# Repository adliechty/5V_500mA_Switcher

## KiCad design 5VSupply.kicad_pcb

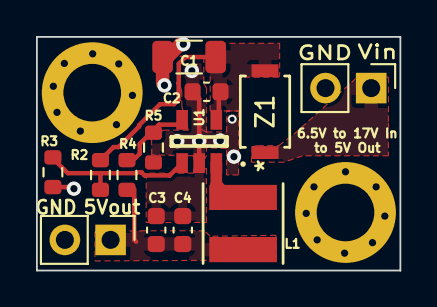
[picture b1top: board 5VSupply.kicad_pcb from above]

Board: 2 copper layers, 20.2 x 13.0 mm, 15 parts (0 on the bottom side), 7 nets.

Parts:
C1: 22uF; C_1206_3216Metric
C2: 0.1uF; C_0603_1608Metric
C3, C4: 10uF; C_0603_1608Metric
H1, H2: DNP; MountingHole_3.2mm_M3_DIN965_Pad
J1, J2: Conn_01x02; PinHeader_1x02_P2.54mm_Vertical
L1: 10uH 1.9A ASPI-0628-100M-T1; IND_SDCL1V4020-3R3M-R_EAT-M
R2: 10k; R_0603_1608Metric
R3: 2.2k; R_0603_1608Metric
R4: 105k; R_0603_1608Metric
R5: 20k; R_0603_1608Metric
U1: TPS560200DBVR; DBV0005A_N
Z1: RSX501LAM20TR; DIO_RB050LAM_ROM

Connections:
/5V_Out: C3.1, C4.1, J2.1, L1.2, R4.1
GND: C1.2, C2.2, C3.2, C4.2, H1.1, H2.1, J1.2, J2.2, R3.2, R5.2, U1.2 (GND)
unnamed: J1.1, Z1.1
unnamed: R2.2, R3.1, U1.1 (EN)
unnamed: L1.1, U1.3 (PH)
unnamed: C1.1, C2.1, R2.1, U1.4 (VIN), Z1.2
unnamed: R4.2, R5.1, U1.5 (VSENSE)

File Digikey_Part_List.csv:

Digikey PN,Reference,Footprint,Value,Voltage,Type,Order Quantity,Total Price
490-GRT31CC71E226ME13KCT-ND,C1,Capacitor_SMD:C_1206_3216Metric,22uF,25V,X5R,1,
490-10431-1-ND ,C2,Capacitor_SMD:C_0603_1608Metric,0.1uF,25V,X5R,1,0.06
490-GRM188R61A106ME69JCT-ND,"C3, C4",Capacitor_SMD:C_0603_1608Metric,10uF,10V,X5R,2,0.03
1212-1089-ND,"J1, J2",1x2FemaleVertical:PinHeader_1x02_P2.54mm_VerticalFemale,Conn_01x02,,,2,0.46
283-SDCL1V4020-100M-RCT-ND,L1,10uFInductor:IND_SDCL1V4020-3R3M-R_EAT-M,10uH 1.9A ASPI-0628-100M-T1,,,1,0.13
13-AC0603DR-0710KLCT-ND,R2,Resistor_SMD:R_0603_1608Metric,10k,,,1,0.02
P2.2KGCT-ND,R3,Resistor_SMD:R_0603_1608Metric,2.2k,,,1,0.08
13-RT0603DRE07105KLCT-ND,R4,Resistor_SMD:R_0603_1608Metric,105k,,THIN,1,0.01
311-2479-1-ND,R5,Resistor_SMD:R_0603_1608Metric,20k,,THIN,1,0.01
296-38559-1-ND,U1,DBV0005A_N,TPS560200DBVR,,,1,0.23
RSX501LAM20CT-ND,Z1,DIO_RB050LAM_ROM,RSX501LAM20TR,,,1,0.11
,,,,,,,
,,,,,,,

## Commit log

2023-11-09 First add
2023-11-10 PCB submitted for order
